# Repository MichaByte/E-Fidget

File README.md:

# E-Fidget

Hi there! There's a lot of moving parts with this project right now,
so why don't you check out [my latest blog post](https://2231puppy.tech/posts/projects/e-fidget/update-3/)
for more info?

Thanks :)

\- Micha

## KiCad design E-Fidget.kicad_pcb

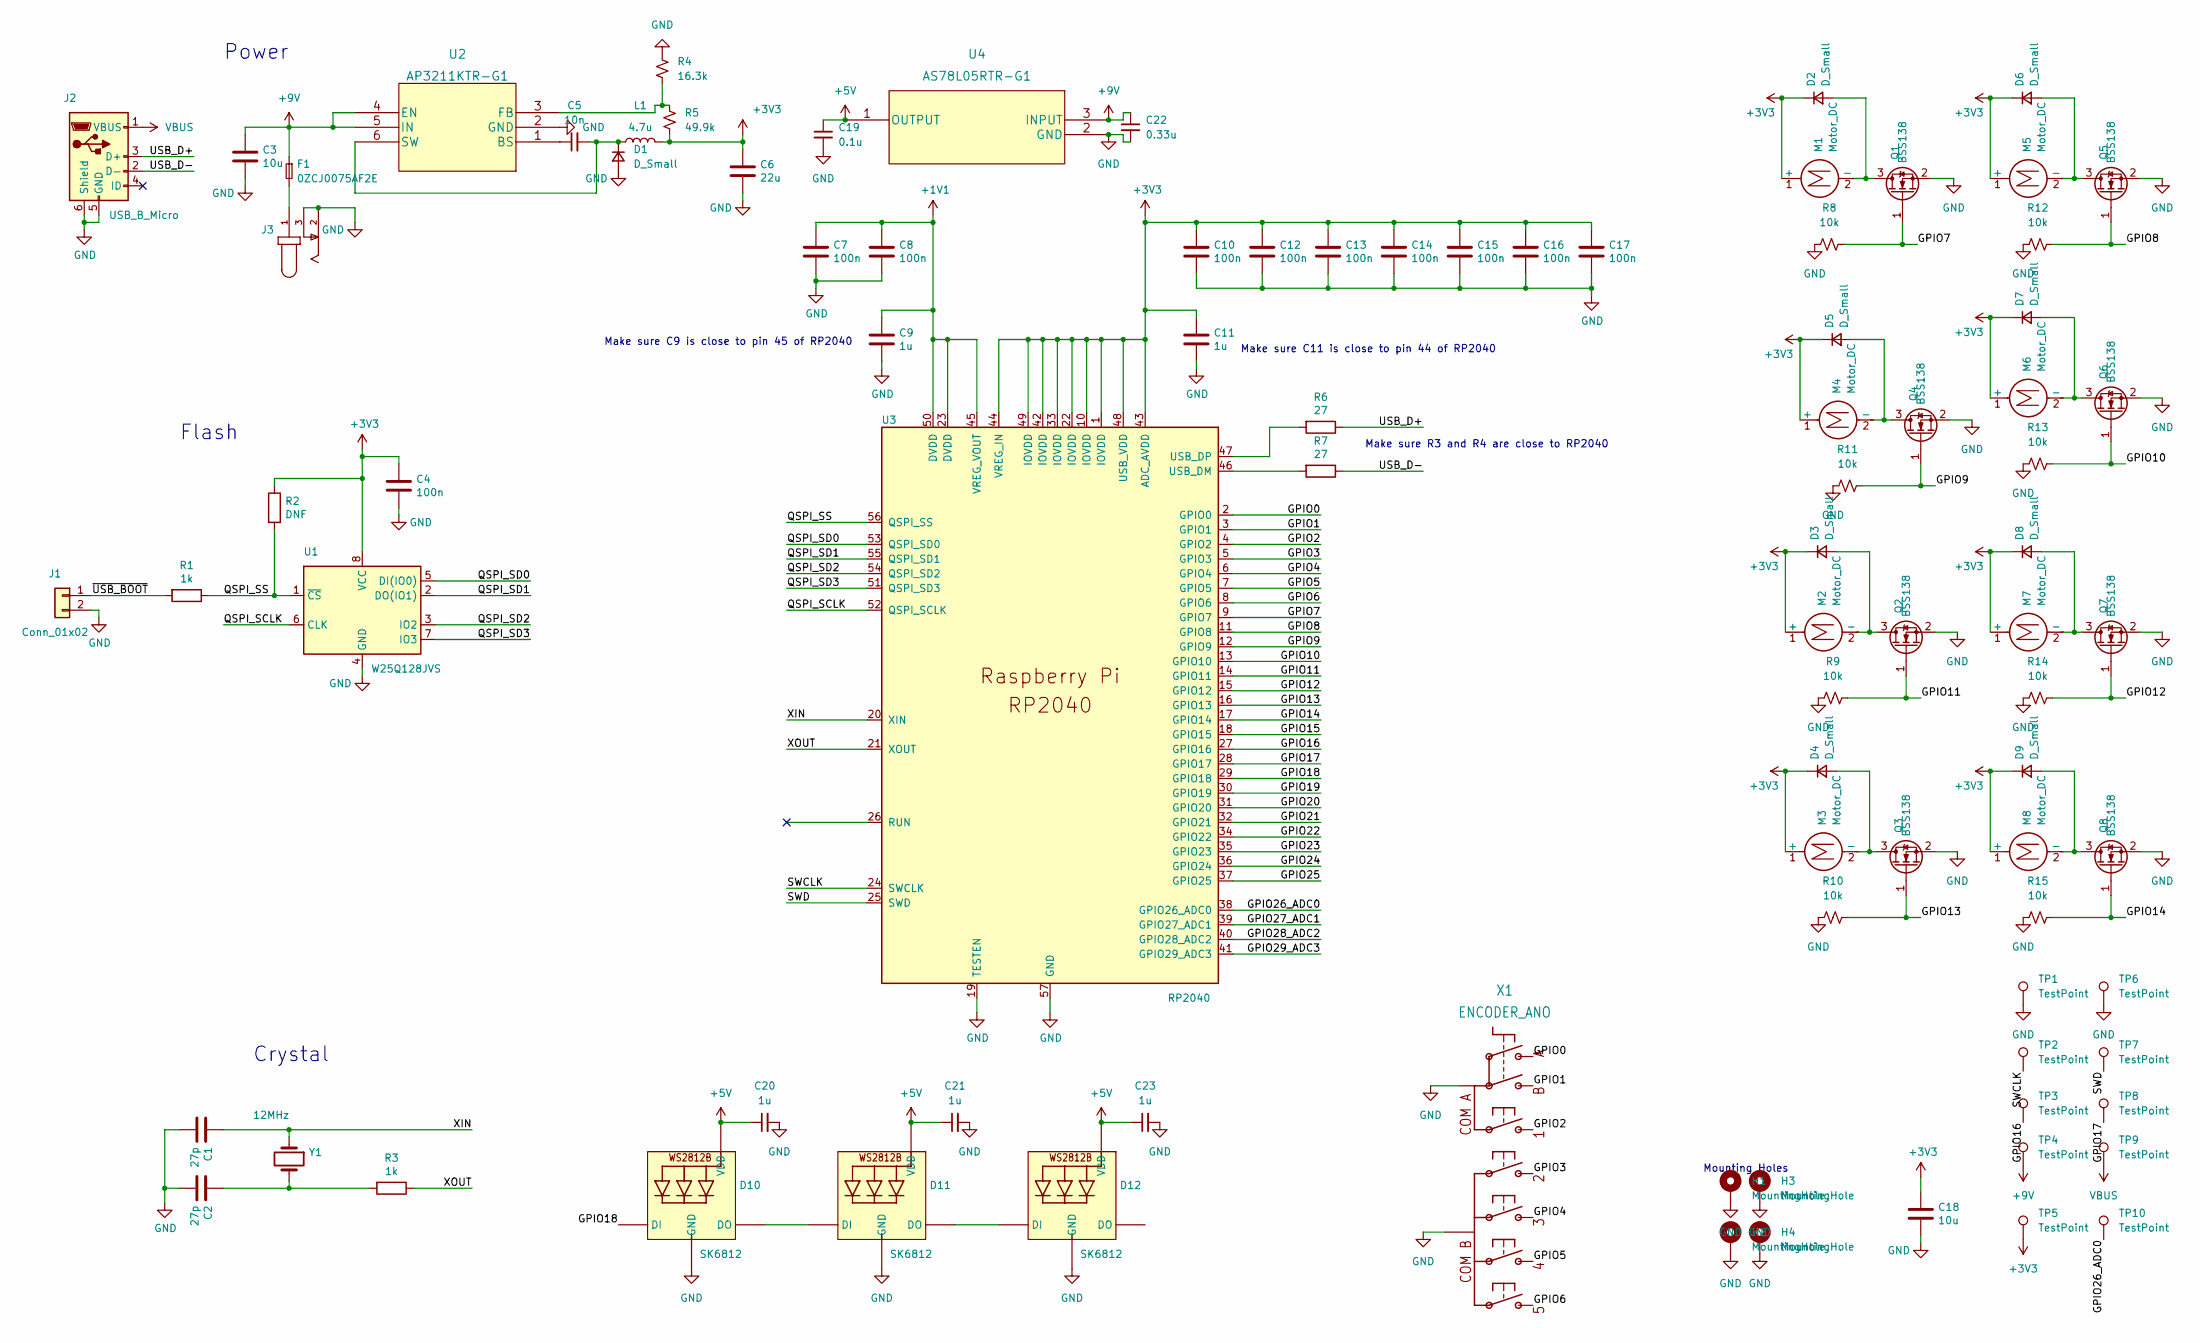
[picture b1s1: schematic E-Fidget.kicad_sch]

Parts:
C1, C2: 27p; C_0402_1005Metric_Pad0.74x0.62mm_HandSolder
C3, C18: 10u; C_0805_2012Metric_Pad1.18x1.45mm_HandSolder
C4, C7, C8, C10, C12, C13, C14, C15, C16, C17: 100n; C_0402_1005Metric_Pad0.74x0.62mm_HandSolder
C5: 10n; C_0805_2012Metric_Pad1.18x1.45mm_HandSolder
C6: 22u; C_0805_2012Metric_Pad1.18x1.45mm_HandSolder
C9, C11: 1u; C_0402_1005Metric_Pad0.74x0.62mm_HandSolder
C19: 0.1u; C_0805_2012Metric_Pad1.18x1.45mm_HandSolder
C20, C21, C23: 1u; C_0805_2012Metric_Pad1.18x1.45mm_HandSolder
C22: 0.33u; C_0805_2012Metric_Pad1.18x1.45mm_HandSolder
D1, D2, D3, D4, D5, D6, D7, D8, D9: D_Small; SC-59_Handsoldering_No_Pin3
D10, D11, D12: SK6812; NEO3535_REVERSE
F1: 0ZCJ0075AF2E; Fuse_1206_3216Metric_Pad1.42x1.75mm_HandSolder
H1, H2, H3, H4: MountingHole; MountingHole_2.2mm_M2_Pad_Via
J1: Conn_01x02; PinHeader_1x02_P2.54mm_Vertical
J2: USB_B_Micro; USB_Micro-B_Amphenol_10103594-0001LF_Horizontal_modified
J3: Barrel_Jack_MountingPin; CUI_PJ-102AH
L1: 4.7u; NR6028T4R7M
M1, M2, M3, M4, M5, M6, M7, M8: Motor_DC; SolderWire-0.1sqmm_1x02_P3.6mm_D0.4mm_OD1mm_Relief
Q1, Q2, Q3, Q4, Q5, Q6, Q7, Q8: BSS138; SOT-323_SC-70_Handsoldering
R1, R3: 1k; R_0805_2012Metric_Pad1.20x1.40mm_HandSolder
R2: DNF; R_0805_2012Metric_Pad1.20x1.40mm_HandSolder
R4: 16.3k; R_0805_2012Metric_Pad1.20x1.40mm_HandSolder
R5: 49.9k; R_0805_2012Metric_Pad1.20x1.40mm_HandSolder
R6, R7: 27; R_0805_2012Metric_Pad1.20x1.40mm_HandSolder
R8: 10k; C_0805_2012Metric_Pad1.18x1.45mm_HandSolder
R9, R10, R11, R12, R13, R14, R15: 10k; R_0805_2012Metric_Pad1.20x1.40mm_HandSolder
TP1, TP2, TP3, TP4, TP5, TP6, TP7, TP8, TP9, TP10: TestPoint; TestPoint_Pad_D2.0mm
U1: W25Q128JVS; SOIC-8_5.23x5.23mm_P1.27mm
U2: AP3211KTR-G1; SOT-23-6_Handsoldering
U3: RP2040; RP2040-QFN-56
U4: AS78L05RTR-G1
X1: ENCODER_ANO
Y1: 12MHz; 445I23D12M00000

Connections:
+1V1: C7.1, C8.1, C9.1, U3.23 (DVDD), U3.45 (VREG_VOUT), U3.50 (DVDD)
+5V: C19.1, C20.1, C21.1, C23.1, D10.1-VDD (VDD), D11.1-VDD (VDD), D12.1-VDD (VDD), U4.1 (OUTPUT)
/GPIO0: U3.2 (GPIO0), X1.A
/GPIO1: U3.3 (GPIO1), X1.B
/GPIO2: U3.4 (GPIO2), X1.S1 (1)
/GPIO3: U3.5 (GPIO3), X1.S2
/GPIO4: U3.6 (GPIO4), X1.S3
/GPIO5: U3.7 (GPIO5), X1.S4
/GPIO6: U3.8 (GPIO6), X1.S5
/GPIO7: Q1.1 (G), R8.2, U3.9 (GPIO7)
/GPIO8: Q5.1 (G), R12.2, U3.11 (GPIO8)
/GPIO9: Q4.1 (G), R11.2, U3.12 (GPIO9)
/GPIO10: Q6.1 (G), R13.2, U3.13 (GPIO10)
/GPIO11: Q2.1 (G), R9.2, U3.14 (GPIO11)
/GPIO12: Q7.1 (G), R14.2, U3.15 (GPIO12)
/GPIO13: Q3.1 (G), R10.2, U3.16 (GPIO13)
/GPIO14: Q8.1 (G), R15.2, U3.17 (GPIO14)
/GPIO15: U3.18 (GPIO15)
/GPIO16: TP3.1, U3.27 (GPIO16)
/GPIO17: TP8.1, U3.28 (GPIO17)
/GPIO18: D10.4-DIN (DI), U3.29 (GPIO18)
/GPIO19: U3.30 (GPIO19)
/GPIO20: U3.31 (GPIO20)
/GPIO21: U3.32 (GPIO21)
/GPIO22: U3.34 (GPIO22)
/GPIO23: U3.35 (GPIO23)
/GPIO24: U3.36 (GPIO24)
/GPIO25: U3.37 (GPIO25)
/GPIO26_ADC0: TP10.1, U3.38 (GPIO26_ADC0)
/GPIO27_ADC1: U3.39 (GPIO27_ADC1)
/GPIO28_ADC2: U3.40 (GPIO28_ADC2)
/GPIO29_ADC3: U3.41 (GPIO29_ADC3)
/QSPI_SCLK: U1.6 (CLK), U3.52 (QSPI_SCLK)
/QSPI_SD0: U1.5 (DI(IO0)), U3.53 (QSPI_SD0)
/QSPI_SD1: U1.2 (DO(IO1)), U3.55 (QSPI_SD1)
/QSPI_SD2: U1.3 (IO2), U3.54 (QSPI_SD2)
/QSPI_SD3: U1.7 (IO3), U3.51 (QSPI_SD3)
/QSPI_SS: R1.1, R2.2, U1.1 (~CS), U3.56 (QSPI_SS)
/SWCLK: TP2.1, U3.24 (SWCLK)
/SWD: TP7.1, U3.25 (SWD)
/USB_D+: J2.3 (D+), R6.1
/USB_D-: J2.2 (D-), R7.1
/XIN: C1.1, U3.20 (XIN), Y1.1
/XOUT: R3.1, U3.21 (XOUT)
/~USB_BOOT: J1.1, R1.2
GND: C1.2, C2.2, C3.2, C4.2, C6.2, C7.2, C8.2, C9.2, C10.2, C11.2, C12.2, C13.2, C14.2, C15.2, C16.2, C17.2, C18.2, C19.2, C20.2, C21.2, C22.2, C23.2, D1.2 (A), D10.3-GND (GND), D11.3-GND (GND), D12.3-GND (GND), H1.1, H2.1, H3.1, H4.1, J1.2, J2.5 (GND), J2.6 (Shield), J3.2, J3.3, Q1.2 (S), Q2.2 (S), Q3.2 (S), Q4.2 (S), Q5.2 (S), Q6.2 (S), Q7.2 (S), Q8.2 (S), R4.1, R8.1, R9.1, R10.1, R11.1, R12.1, R13.1, R14.1, R15.1, TP1.1, TP6.1, U1.4 (GND), U2.2 (GND), U3.19 (TESTEN), U3.57 (GND), U4.2 (GND), X1.COM_A (COMA), X1.COM_B
unnamed: C2.1, R3.2, Y1.2
unnamed: C5.1, U2.1 (BS)
unnamed: C5.2, D1.1 (K), L1.1, U2.6 (SW)
unnamed: D2.2 (A), M1.2 (-), Q1.3 (D)
unnamed: D3.2 (A), M2.2 (-), Q2.3 (D)
unnamed: D4.2 (A), M3.2 (-), Q3.3 (D)
unnamed: D5.2 (A), M4.2 (-), Q4.3 (D)
unnamed: D6.2 (A), M5.2 (-), Q5.3 (D)
unnamed: D7.2 (A), M6.2 (-), Q6.3 (D)
unnamed: D8.2 (A), M7.2 (-), Q7.3 (D)
unnamed: D9.2 (A), M8.2 (-), Q8.3 (D)
unnamed: D10.2-DOUT (DO), D11.4-DIN (DI)
unnamed: D11.2-DOUT (DO), D12.4-DIN (DI)
unnamed: F1.2, J3.1
unnamed: R4.2, R5.1, U2.3 (FB)
unnamed: R6.2, U3.47 (USB_DP)
unnamed: R7.2, U3.46 (USB_DM)
VBUS: J2.1 (VBUS), TP9.1

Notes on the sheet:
Power
Crystal
Make sure C11 is close to pin 44 of RP2040
Make sure R3 and R4 are close to RP2040
Make sure C9 is close to pin 45 of RP2040
Flash
Mounting Holes

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
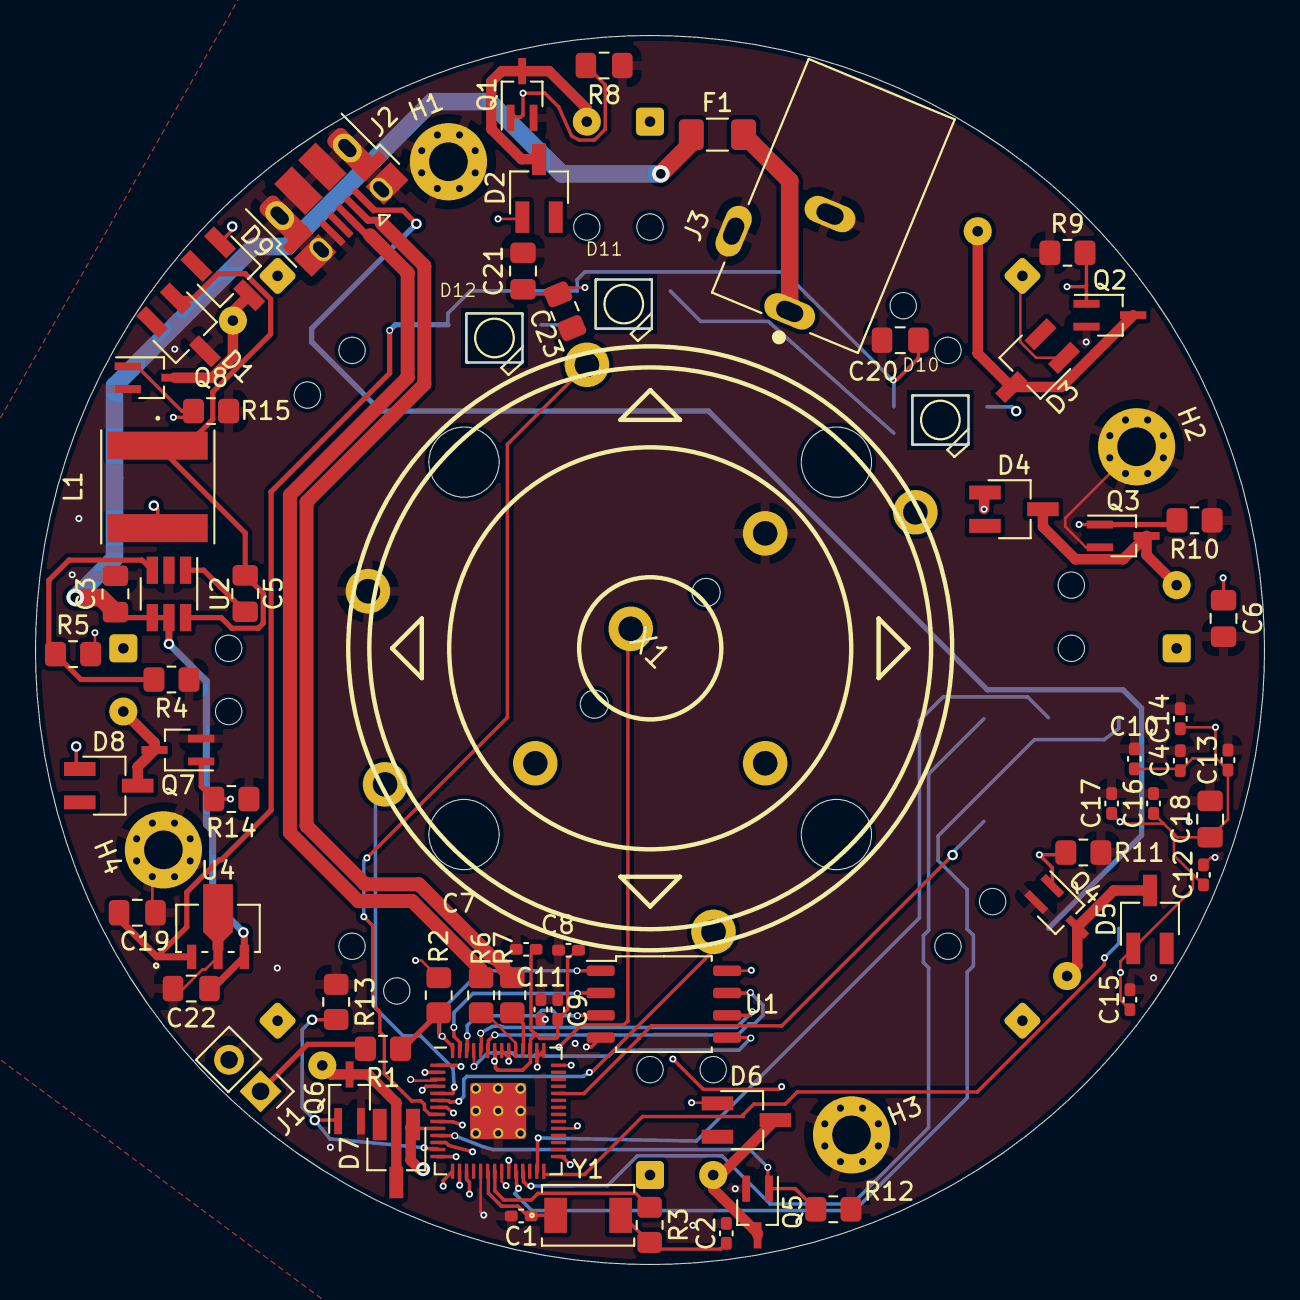
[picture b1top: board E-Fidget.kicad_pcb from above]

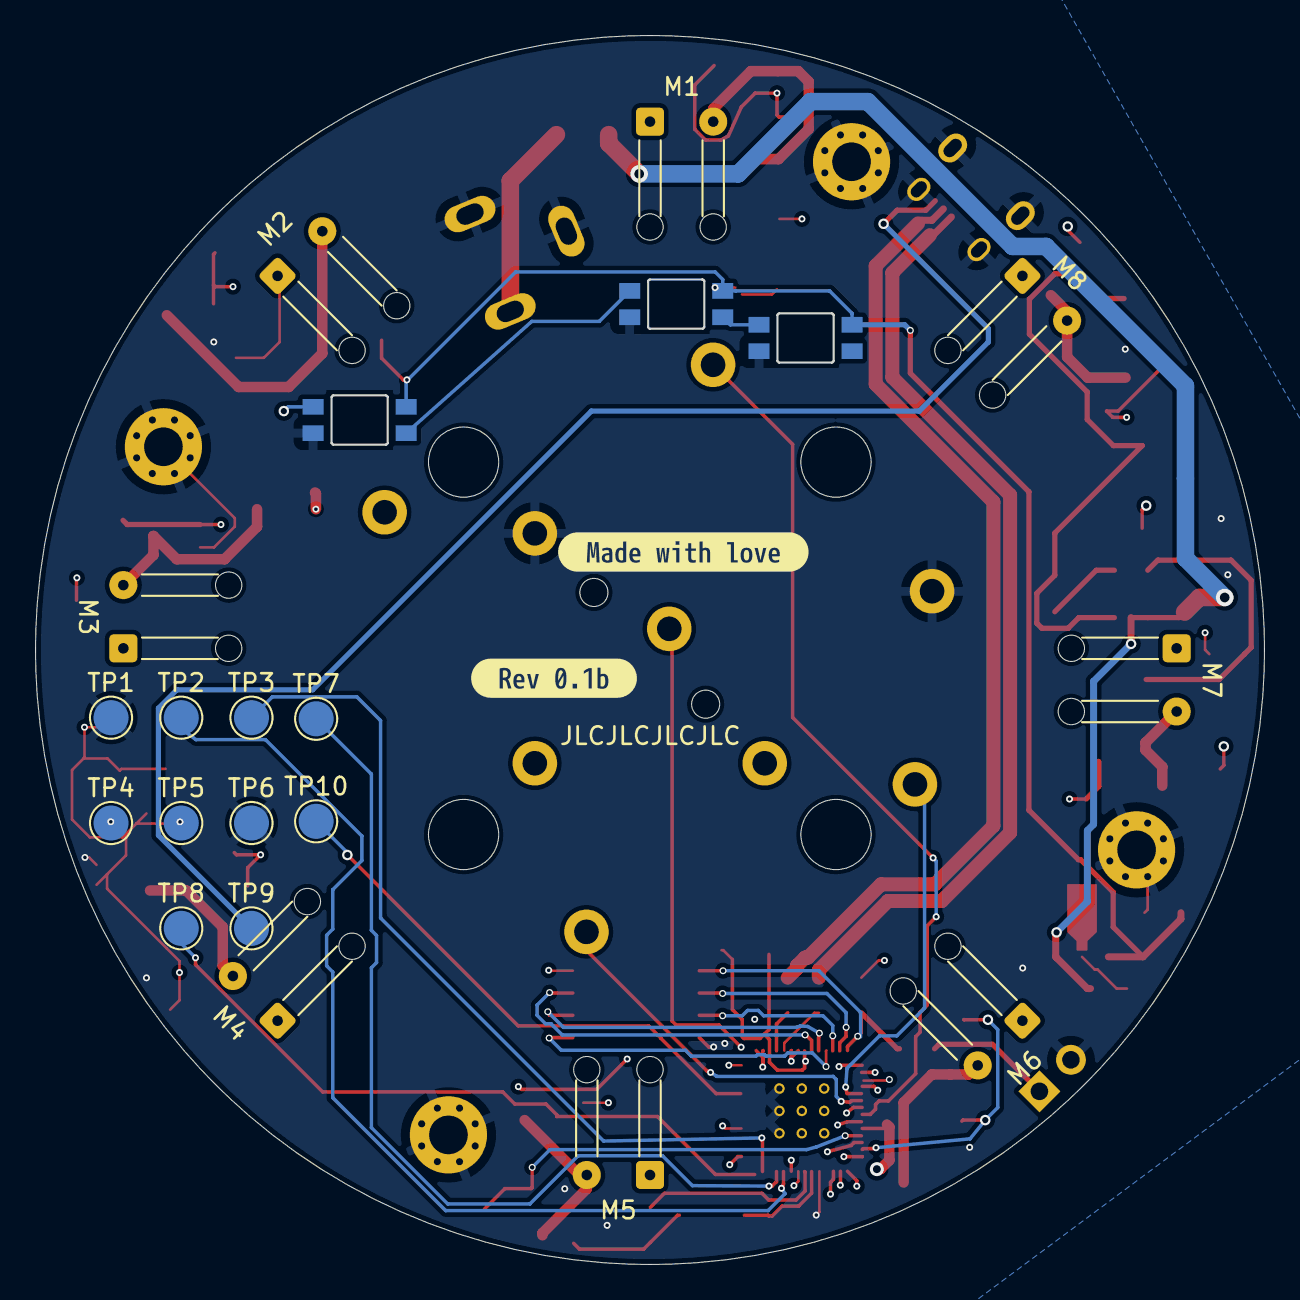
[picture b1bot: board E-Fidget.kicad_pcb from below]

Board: 4 copper layers, 69.9 x 69.9 mm, 93 parts (20 on the bottom side), 55 nets.

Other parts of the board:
kibuzzard-6304F62D: G***; kibuzzard-6304F62D
kibuzzard-6302439D: G***; kibuzzard-6302439D

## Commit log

2022-08-16 Route some traces (56 unrouted pads)
2022-08-23 Finish routing traces & fix DRC errors
2022-08-23 Add some text to the bottom silkscreen
    Added the revision (0.1b) and "JLCJLCJLCJLC" to tell JLCPCB where to place the order number.
2022-08-24 Add images
2022-08-25 [ImgBot] Optimize images
    *Total -- 342.66kb -> 234.83kb (31.47%)
    /img/E-Fidget-Back.jpg -- 147.80kb -> 93.67kb (36.62%)
    /img/E-Fidget-Front.jpg -- 194.86kb -> 141.17kb (27.55%)
2022-12-13 Switch to MIT license
2022-12-23 Do some minor cleanup
2023-01-02 Make soldermask purple
2023-04-23 Restructure & update to V3
2023-04-23 Attempt to add docs
2023-04-23 Take two at adding docs
2023-04-23 Create CNAME
2023-04-23 Fix workfow file
2023-04-23 Fix gitignore gitignoring html
2023-04-23 Change "docs" to "Documentation"
2023-04-23 Update MkDocs workflow to use custom version for now
2023-04-23 Move CNAME into docs_dir
2023-04-23 Undo workflow changes
2023-04-23 [ImgBot] Optimize images
    *Total -- 1,386.12kb -> 1,350.43kb (2.57%)
    /Hardware/battery.svg -- 1.84kb -> 0.49kb (73.35%)
    /Hardware/outline.svg -- 2.12kb -> 0.62kb (70.56%)
    /Hardware/layer1.svg -- 0.72kb -> 0.44kb (38.75%)
    /Hardware/E-Fidget V3.png -- 865.31kb -> 833.31kb (3.7%)
    /Documentation/docs/img/favicons/android-chrome-512x512.png -- 22.90kb -> 22.77kb (0.6%)
2023-04-23 Deployed 542cff4 with MkDocs version: 1.4.2
2023-04-27 Start programming guide
2023-04-27 Update hardware info in docs
2023-04-27 Change some code variables
2023-04-27 Update copyright year
2023-04-28 Move Arduino sketch into a folder
2023-04-28 Start work on v3.1
2023-05-01 v3.1 cont.
2023-05-01 Rename to V4
2023-05-04 Big firmware changes, restructured, better power usage

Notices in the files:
parts and their libraries:
Copyright 2021 Accelerated Designs. All rights reserved.
